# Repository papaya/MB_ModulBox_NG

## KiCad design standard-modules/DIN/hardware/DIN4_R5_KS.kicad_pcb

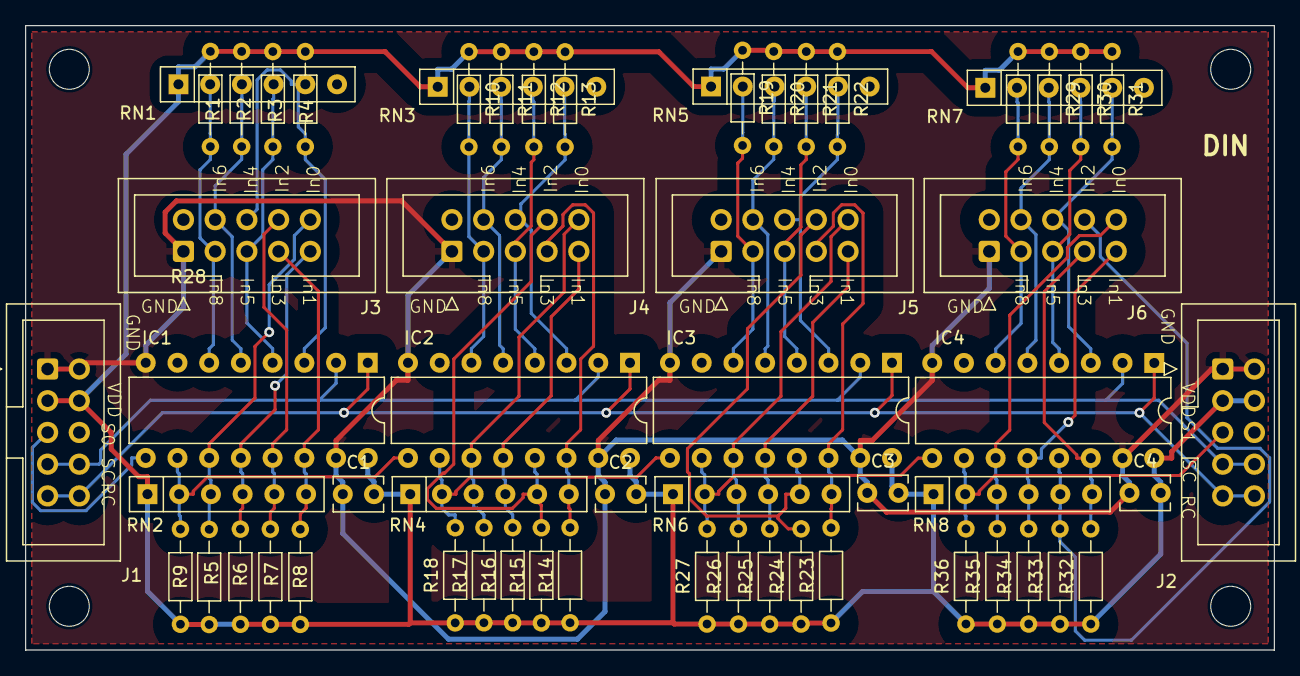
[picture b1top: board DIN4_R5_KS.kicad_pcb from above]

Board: 2 copper layers, 100.0 x 50.0 mm, 62 parts (0 on the bottom side), 41 nets.

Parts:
C1, C2, C3, C4: 100nf; C_Disc_D3.8mm_W2.6mm_P2.50mm
H1, H2, H3, H4: MountingHole; MountingHole_3.2mm_M3
IC1, IC2, IC3, IC4: 74HC165; DIP-16_W7.62mm
J1, J2: sin_in; IDC-Header_2x05_P2.54mm_Vertical_ksr_TO_J8_J9
J3, J4, J5, J6: sin_in; IDC-Header_2x05_P2.54mm_Vertical_ksr_dIN
R1, R2, R3, R4, R5, R6, R7, R8, R9, R10, R11, R12, R13, R14, R15, R16, R17, R18, R19, R20, R21, R22, R23, R24, R25, R26, R27, R28, R29, R30, R31, R32, R33, R34, R35, R36: 10k; R_Axial_DIN0204_L3.6mm_D1.6mm_P7.62mm_Horizontal
RN1, RN2, RN3, RN4, RN5, RN6, RN7, RN8: R_Network05; R_Array_SIP6

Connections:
+5V: C1.2, C2.2, C3.2, C4.2, IC1.16 (VCC), IC2.16 (VCC), IC3.16 (VCC), IC4.16 (VCC), J1.3, J1.4, J2.3, J2.4, R1.1, R2.1, R3.1, R4.1, R5.1, R6.1, R7.1, R8.1, R9.1, R10.1, R11.1, R12.1, R13.1, R14.1, R15.1, R16.1, R17.1, R18.1, R19.1, R20.1, R21.1, R22.1, R23.1, R24.1, R25.1, R26.1, R27.1, R28.1, R29.1, R30.1, R31.1, R32.1, R33.1, R34.1, R35.1, R36.1, RN1.1 (common), RN2.1 (common), RN3.1 (common), RN4.1 (common), RN5.1 (common), RN6.1 (common), RN7.1 (common), RN8.1 (common)
GND: C1.1, C2.1, C3.1, C4.1, IC1.8 (GND), IC1.15 (~CE), IC2.8 (GND), IC2.15 (~CE), IC3.8 (GND), IC3.15 (~CE), IC4.8 (GND), IC4.15 (~CE), J1.1, J1.2, J2.1, J2.2, J3.1, J4.1, J5.1, J6.1
unnamed: IC1.11 (D0), J3.10, R5.2, RN2.3 (R2)
unnamed: IC1.12 (D1), J3.9, R6.2, RN2.4 (R3)
unnamed: IC1.13 (D2), J3.8, R7.2, RN2.5 (R4)
unnamed: IC1.14 (D3), J3.7, R8.2, RN2.6 (R5)
unnamed: IC1.3 (D4), J3.6, R4.2, RN1.5 (R4)
unnamed: IC1.4 (D5), J3.5, R3.2, RN1.4 (R3)
unnamed: IC1.5 (D6), J3.4, R2.2, RN1.3 (R2)
unnamed: IC1.6 (D7), J3.3, R1.2, RN1.2 (R1)
unnamed: IC1.10 (DS), IC2.9 (Q7), R9.2, RN2.2 (R1)
unnamed: IC1.9 (Q7), J1.5
unnamed: IC2.11 (D0), J4.10, R17.2, RN4.3 (R2)
unnamed: IC2.12 (D1), J4.9, R16.2, RN4.4 (R3)
unnamed: IC2.13 (D2), J4.8, R15.2, RN4.5 (R4)
unnamed: IC2.14 (D3), J4.7, R14.2, RN4.6 (R5)
unnamed: IC2.3 (D4), J4.6, R13.2, RN3.5 (R4)
unnamed: IC2.4 (D5), J4.5, R12.2, RN3.4 (R3)
unnamed: IC2.5 (D6), J4.4, R11.2, RN3.3 (R2)
unnamed: IC2.6 (D7), J4.3, R10.2, RN3.2 (R1)
unnamed: IC2.10 (DS), IC3.9 (Q7), R18.2, RN4.2 (R1)
unnamed: IC3.11 (D0), J5.10, R26.2, RN6.3 (R2)
unnamed: IC3.12 (D1), J5.9, R25.2, RN6.4 (R3)
unnamed: IC3.13 (D2), J5.8, R24.2, RN6.5 (R4)
unnamed: IC3.14 (D3), J5.7, R23.2, RN6.6 (R5)
unnamed: IC3.3 (D4), J5.6, R22.2, RN5.5 (R4)
unnamed: IC3.4 (D5), J5.5, R21.2, RN5.4 (R3)
unnamed: IC3.5 (D6), J5.4, R20.2, RN5.3 (R2)
unnamed: IC3.6 (D7), J5.3, R19.2, RN5.2 (R1)
unnamed: IC3.10 (DS), IC4.9 (Q7), R27.2, RN6.2 (R1)
unnamed: IC4.11 (D0), J6.10, R35.2, RN8.3 (R2)
unnamed: IC4.12 (D1), J6.9, R34.2, RN8.4 (R3)
unnamed: IC4.13 (D2), J6.8, R33.2, RN8.5 (R4)
unnamed: IC4.14 (D3), J6.7, R32.2, RN8.6 (R5)
unnamed: IC4.3 (D4), J6.6, R31.2, RN7.5 (R4)
unnamed: IC4.4 (D5), J6.5, R30.2, RN7.4 (R3)
unnamed: IC4.5 (D6), J6.4, R29.2, RN7.3 (R2)
unnamed: IC4.6 (D7), J6.3, R28.2, RN7.2 (R1)
unnamed: IC4.10 (DS), J2.5, R36.2, RN8.2 (R1)
RC: IC1.1 (~PL), IC2.1 (~PL), IC3.1 (~PL), IC4.1 (~PL), J1.9, J1.10, J2.9, J2.10
SC: IC1.2 (CP), IC2.2 (CP), IC3.2 (CP), IC4.2 (CP), J1.7, J1.8, J2.7, J2.8

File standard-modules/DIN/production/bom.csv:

Designator,Footprint,Quantity,Value,LCSC Part #
"C1, C2, C3, C4",C_Disc_D3.8mm_W2.6mm_P2.50mm,4,100nf,C14663
"H1, H2, H3, H4",MountingHole_3.2mm_M3,4,MountingHole,
"IC1, IC2, IC3, IC4",DIP-16_W7.62mm,4,74HC165,C5613
"J1, J2",IDC-Header_2x05_P2.54mm_Vertical_ksr_TO_J8_J9,2,sin_in,
"J3, J4, J5, J6",IDC-Header_2x05_P2.54mm_Vertical_ksr_dIN,4,sin_in,
"R1, R10, R11, R12, R13, R14, R15, R16, R17, R18, R19, R2, R20, R21, R22, R23, R24, R25, R26, R27, R28, R29, R3, R30, R31, R32, R33, R34, R35, R36, R4, R5, R6, R7, R8, R9",R_Axial_DIN0204_L3.6mm_D1.6mm_P7.62mm_Horizontal,36,10k,C1035
"RN1, RN2, RN3, RN4, RN5, RN6, RN7, RN8",R_Array_SIP6,8,R_Network05,

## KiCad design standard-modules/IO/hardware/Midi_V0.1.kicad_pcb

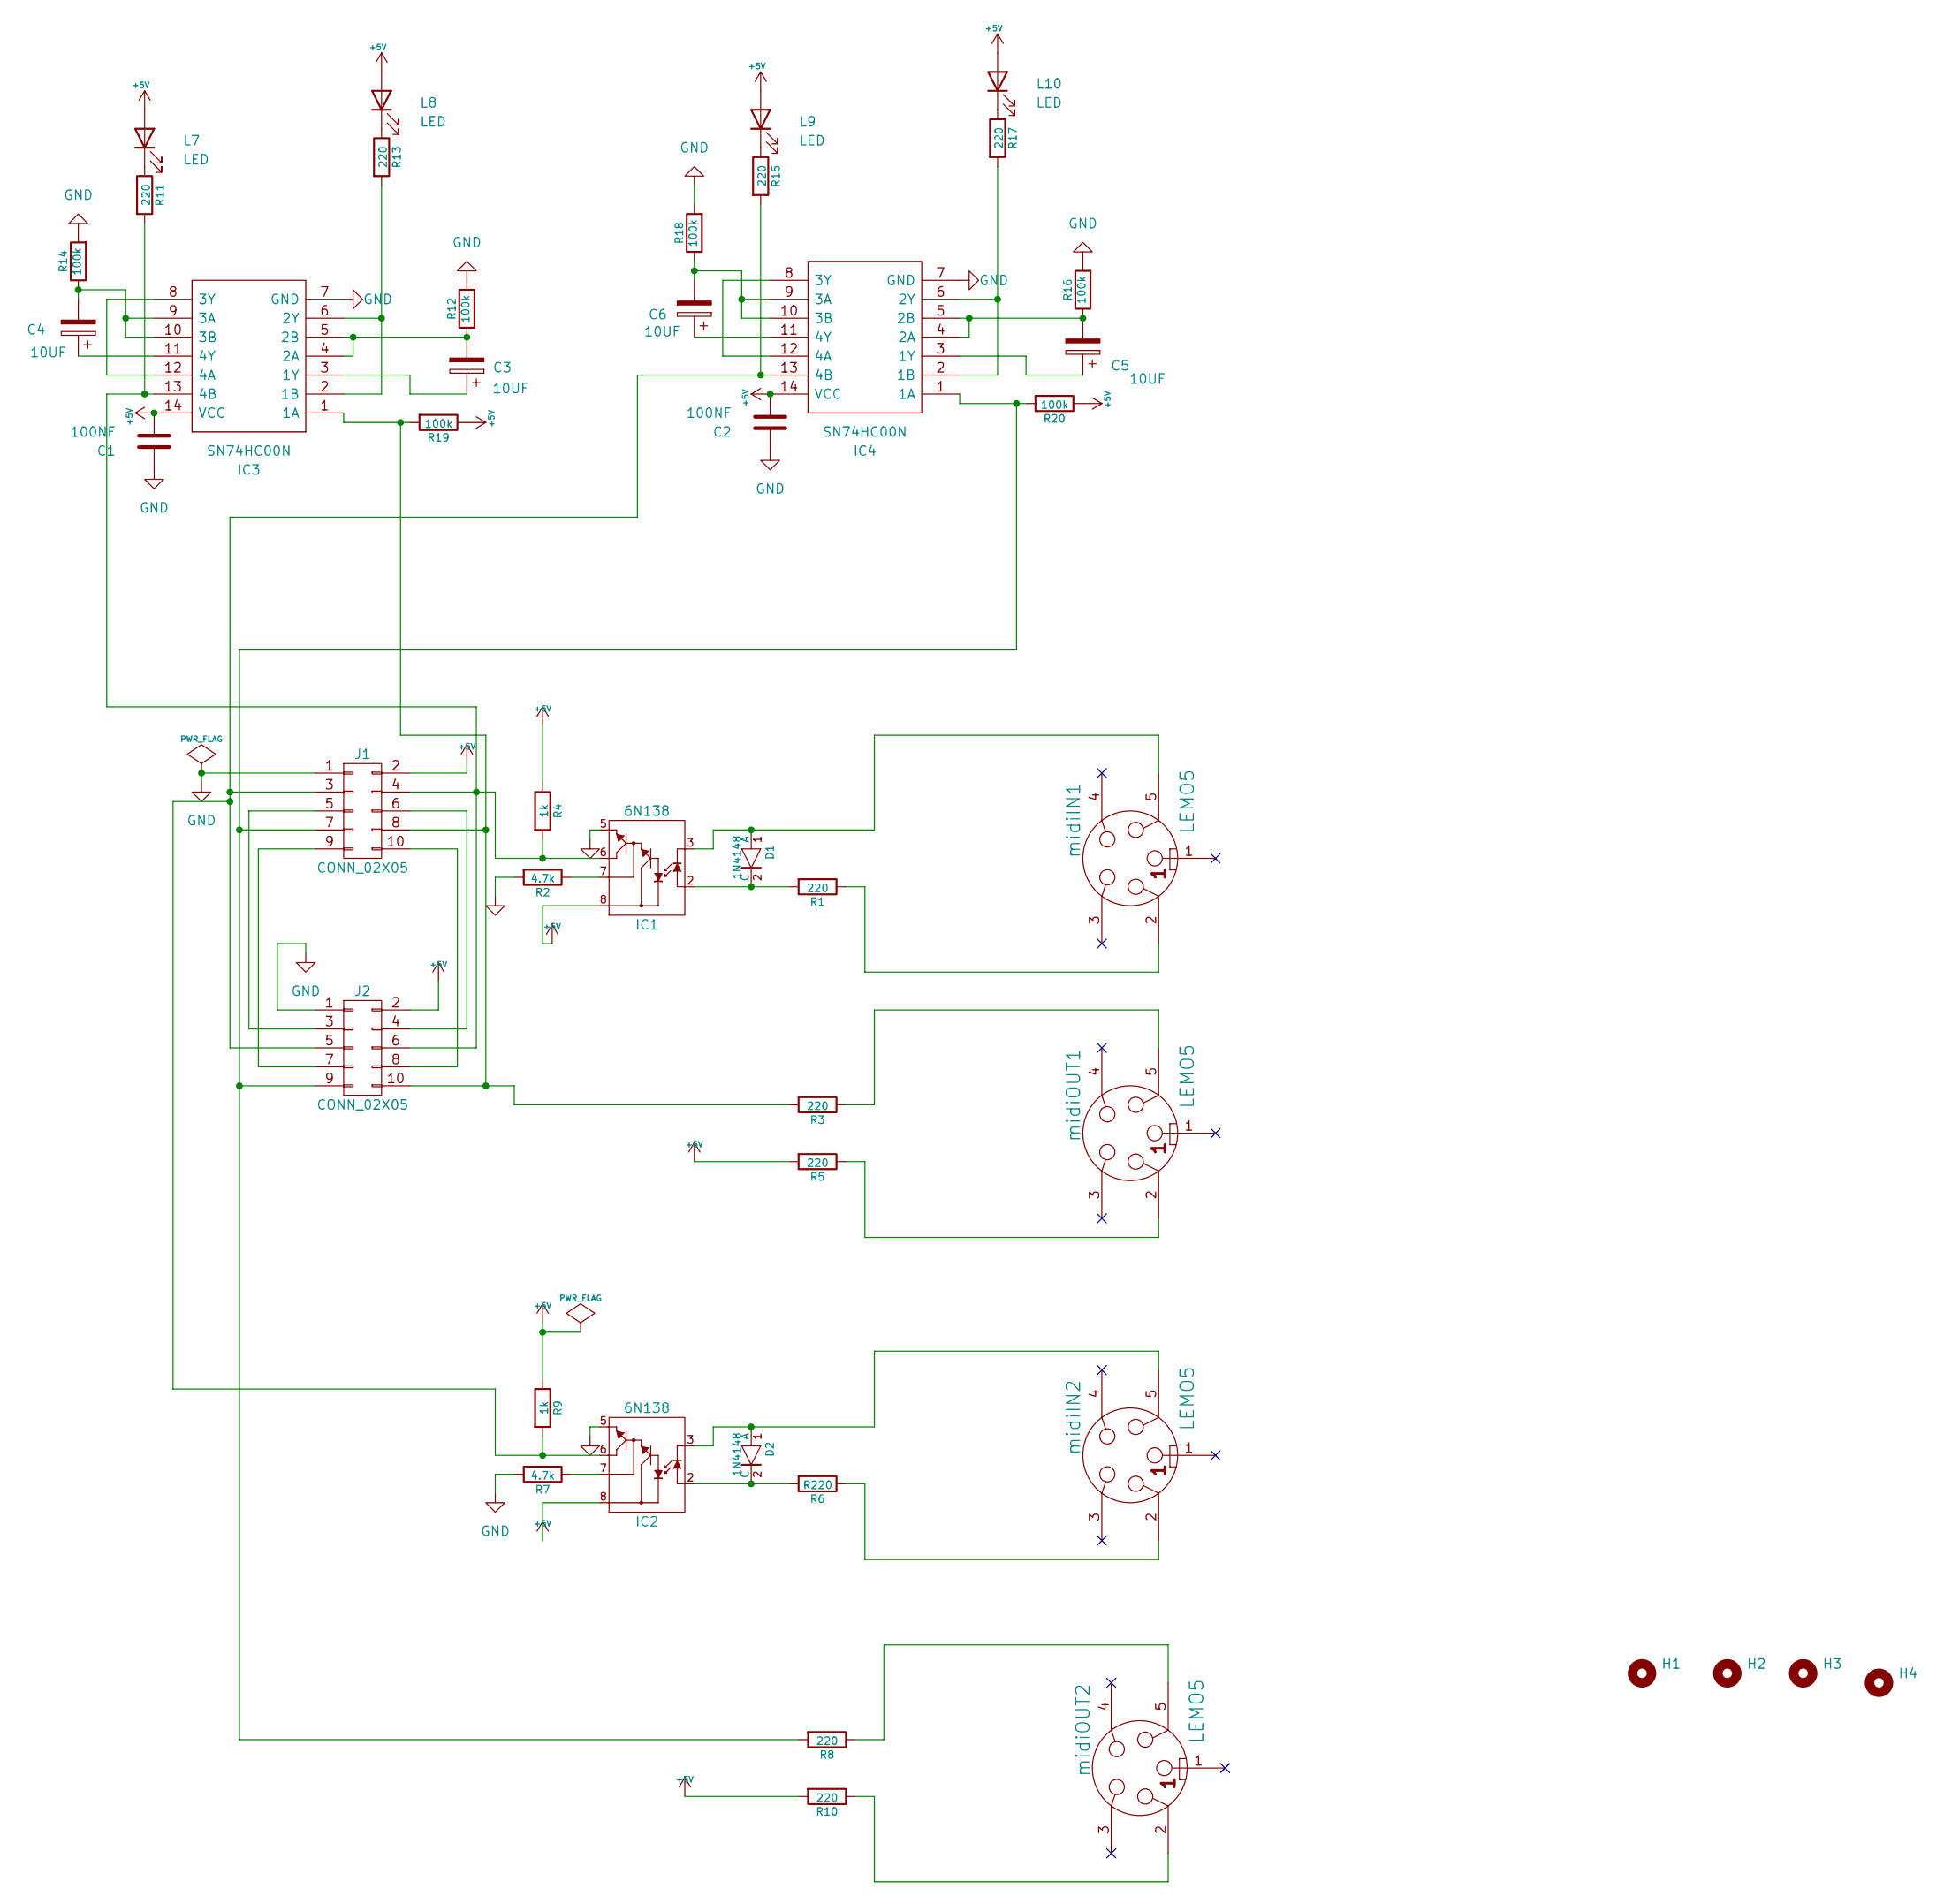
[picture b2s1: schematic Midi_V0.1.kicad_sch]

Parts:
C1, C2: 100NF; C_Disc_D3.0mm_W2.0mm_P2.50mm
C3, C4, C5, C6: 10UF; CP_Radial_D5.0mm_P2.00mm
D1, D2: 1N4148; D_DO-35_SOD27_P7.62mm_Horizontal
H1, H2, H3, H4: MountingHole; MountingHole_3.2mm_M3_DIN965_Pad
IC1, IC2: 6N138; DIP-8_W7.62mm_LongPads
IC3, IC4: SN74HC00N; DIP-14_W7.62mm_Socket_LongPads; Mouser Part Number 595-SN74HC00N
J1, J2: CONN_02X05; IDC-Header_2x05_P2.54mm_Vertical
L7, L8, L9, L10: LED; LED_D5.0mm
R1, R3, R5, R8, R10, R11, R13, R15, R17: 220; R_Axial_DIN0204_L3.6mm_D1.6mm_P5.08mm_Horizontal
R2, R7: 4.7k; R_Axial_DIN0204_L3.6mm_D1.6mm_P5.08mm_Horizontal
R4, R9: 1k; R_Axial_DIN0204_L3.6mm_D1.6mm_P5.08mm_Horizontal
R6: R220; R_Axial_DIN0204_L3.6mm_D1.6mm_P5.08mm_Horizontal
R12, R14, R16, R18, R19, R20: 100k; R_Axial_DIN0204_L3.6mm_D1.6mm_P5.08mm_Horizontal
midiIN1, midiIN2: LEMO5; din-5
midiOUT1, midiOUT2: LEMO5; din-5

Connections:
+5V: C1.2, C2.2, IC1.8 (Vcc), IC2.8 (Vcc), IC3.14 (VCC), IC4.14 (VCC), J1.2, J2.2, L7.2 (A), L8.2 (A), L9.2 (A), L10.2 (A), R4.1, R5.2, R9.1, R10.2, R19.1, R20.1
GND: C1.1, C2.1, IC1.5 (GND), IC2.5 (GND), IC3.7 (GND), IC4.7 (GND), J1.1, J2.1, R2.2, R7.2, R12.2, R14.2, R16.2, R18.2
unnamed: D1.1 (A), IC1.3 (K), midiIN1.5
unnamed: D1.2 (C), IC1.2 (A), R1.2
unnamed: D2.1 (A), IC2.3 (K), midiIN2.5
unnamed: D2.2 (C), IC2.2 (A), R6.2
unnamed: IC1.7 (Vb), R2.1
unnamed: IC1.6 (Vo), IC3.13 (4B), J1.4, J2.6, R4.2, R11.2
unnamed: IC2.7 (Vb), R7.1
unnamed: IC2.6 (Vo), IC4.13 (4B), J1.3, J2.5, R9.2, R15.2
unnamed: IC3.1 (1A), J1.8, J2.10, R3.2, R19.2
unnamed: IC3.2 (1B), IC3.6 (2Y), R13.2
unnamed: C3.1, IC3.3 (1Y)
unnamed: C3.2, IC3.4 (2A), IC3.5 (2B), R12.1
unnamed: C4.2, IC3.9 (3A), IC3.10 (3B), R14.1
unnamed: IC3.8 (3Y), IC3.12 (4A)
unnamed: C4.1, IC3.11 (4Y)
unnamed: IC4.1 (1A), J1.7, J2.9, R8.2, R20.2
unnamed: IC4.2 (1B), IC4.6 (2Y), R17.2
unnamed: C5.1, IC4.3 (1Y)
unnamed: C5.2, IC4.4 (2A), IC4.5 (2B), R16.1
unnamed: C6.2, IC4.9 (3A), IC4.10 (3B), R18.1
unnamed: IC4.8 (3Y), IC4.12 (4A)
unnamed: C6.1, IC4.11 (4Y)
unnamed: J1.5, J2.3
unnamed: J1.6, J2.4
unnamed: J1.9, J2.7
unnamed: J1.10, J2.8
unnamed: L7.1 (K), R11.1
unnamed: L8.1 (K), R13.1
unnamed: L9.1 (K), R15.1
unnamed: L10.1 (K), R17.1
unnamed: R1.1, midiIN1.2
unnamed: R3.1, midiOUT1.5
unnamed: R5.1, midiOUT1.2
unnamed: R6.1, midiIN2.2
unnamed: R8.1, midiOUT2.5
unnamed: R10.1, midiOUT2.2

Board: 2 copper layers, 46 parts (0 on the bottom side), 38 nets, no tracks yet.
